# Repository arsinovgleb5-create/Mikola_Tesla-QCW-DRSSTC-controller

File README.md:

# QCW DRSSTC controller v5.9 (ESP32) — firmware, display and control board

**Author: Mikola_Tesla · License: [CC BY 4.0](https://creativecommons.org/licenses/by/4.0/)** — share and adapt freely, just credit the author (see `LICENSE`).

A hand-held controller ("interrupter + ramp generator") for a QCW DRSSTC Tesla coil.
An ESP32 DevKit generates the ramp envelope for the buck modulator and the interrupter
gate signal, reads seven knobs and three buttons, and shows the ramp shape on a small
touch-screen board (ESP32-2432S028R, "Cheap Yellow Display"). Both signals leave the
controller over plastic optical fiber (HFBR transmitters), so the controller has no
galvanic connection to the bridge.

Everything here is hand-made-friendly: a single-sided PCB for toner transfer, through-hole
resistors, DIP drivers, wide tracks and holes.

```
firmware/
  generator/QCW_GENERATOR_ESP32/QCW_GENERATOR_ESP32.ino   ramp generator + interrupter (ESP32 DevKit V1, 30-pin)
  display/cyd_ramp_view/cyd_ramp_view.ino                 ramp viewer for the CYD display (I2C slave)
  display/cyd_ramp_view/User_Setup_CYD.h                  TFT_eSPI configuration for the CYD board
hardware/control_board/
  kicad/                                                  KiCad 10 project (schematic + PCB + own libraries)
  output/schematic.pdf, schematic.png                     schematic, rev. E
  output/bottom_copper_1to1.pdf (+ _mirrored)             copper artwork 1:1 for toner transfer
  output/top_assembly.pdf, bottom_assembly.pdf            part placement, jumper wires (red), labels
  output/top_silkscreen_1to1.pdf, drill_map.pdf           optional silkscreen print, drill map
  output/gerbers.zip                                      Gerber + Excellon in case you order the board
  output/BOM.csv, jumper_wires.json                       parts list, jumper wire list
  output/3d_top.png, 3d_bottom.png, bottom_copper.png     pictures
```

## 1. How the system is put together

```
 knobs (7 pots) ----\
 FIRE / AUTO -------+--> ESP32 DevKit --> TC4420 U2 --> fiber TX "RAMP"  ~~~~> driver board (buck modulator)
 E-STOP (2 groups) -/        |     \---> TC4420 U1 --> fiber TX "INT"   ~~~~> driver board (bridge enable)
                             |  I2C
                             v
                    CYD display (ramp preview, status, supply voltmeter)
```

* **Ramp** — PWM on GPIO19 (MCPWM, 25 kHz carrier by default, `PWM_TOP`). The duty cycle follows the
  envelope: a "wick" step at the start, a rise to the peak, a knee, then a fall. The buck modulator on the
  driver board turns this PWM into the bus voltage envelope.
* **Interrupter** — GPIO4, enables the bridge for the duration of the pulse.
* **One mode**: single QCW ramp pulses, fired by FIRE or repeated by AUTO at the BPS rate (0.5 … 15 pulses/s).
* **E-STOP** — one mushroom switch with two contact groups. Group A (normally open) pulls GPIO23 to ground;
  that pin is also the MCPWM hardware fault input, so the ramp stops in hardware before software reacts.
  Group B (normally closed) is wired in series with the interrupter driver input and cuts the bridge enable
  signal physically.
* **Display link** — I2C, 250 kHz (`LINK_FREQ_HZ`, the same value in both sketches; lower it if your cable is
  long), the generator is the master, the display is a slave at address 0x2A. The link is one-way: the display
  only draws what it receives. Without a STATUS frame for 2 s the display shows OFFLINE / NO LINK.
* **Supply voltmeter** — the display shows the controller 5 V rail (divider on the control board), so a sagging
  battery/buck output is visible before the ESP32 browns out.

## 2. Control board

Single-sided, 85 x 72 mm, all copper on the bottom. Tracks 0.8 mm, clearance 0.6 mm, ground pour on the bottom
with thermal reliefs. Holes: pin headers 1.1 mm, DIP/resistors 1.0 mm, screw terminal 1.6 mm, four M4 mounting
holes (4.3 mm) at (5,6), (80,6), (4.5,67.5), (81,63) mm from the top-left corner.

Parts on top: ESP32 DevKit V1 30-pin in two 1x15 socket headers, two TC4420 DIP-8 drivers, 13 through-hole
resistors 0.25 W (7.62 mm pitch), pin headers, a 2-way screw terminal. Five capacitors (C8…C12) are SMD 1206
and are soldered on the copper (bottom) side — the only SMD parts. See `output/BOM.csv`.

Where tracks cannot cross on one layer, insulated **jumper wires** run on the top side: 30 short pieces
through 29 holes (0.8 mm), the longest one 26 mm. Both ends of one wire carry the same label on the board
(`W1 GND`, `W2 SCL`, …, `W11 ESTOP_B2`); `output/jumper_wires.json` lists every segment with coordinates and
`output/top_assembly.pdf` shows them in red. Holes labelled with the same `Wn` are joined by one wire, chain style.

Making it by toner transfer: print `bottom_copper_1to1.pdf` at 100 % (it is drawn as seen from the top, so
laying the print face-down on the bottom copper mirrors it correctly; use the `_mirrored` file if your
process needs the opposite). Etch, drill, solder the SMD capacitors first, then the jumper wires, then
resistors, sockets, headers and the terminal. Before inserting the ESP32 check that +5V–GND and 3V3–GND are not
shorted.

### Connectors (all 2.54 mm pin headers except J9)

| Conn. | Function | Pins | Location |
|---|---|---|---|
| J1 | knobs (1x9) | 1 = 3V3 rail, 2 = AMPL, 3 = WICK, 4 = FALL, 5 = U, 6 = PW, 7 = BPS, 8 = T, 9 = GND rail | left edge |
| J3 | AUTO button | 1 = signal (GPIO17), 2 = GND | top edge |
| J2 | FIRE button | 1 = signal (GPIO16), 2 = GND | top edge |
| J4 | E-STOP group A (NO) | 1 = GPIO23 (ESTOP_A), 2 = GND | top edge |
| J5 | display (1x5) | 1 = GND, 2 = SCL, 3 = SDA, 4 = VM (voltmeter), 5 = +5V | top edge |
| J8 | E-STOP group B (NC) | 1, 2 = in series with U1 input (no polarity) | bottom edge |
| J7 | fiber TX "INT" (bridge enable) | A = anode, K = cathode | bottom edge |
| J6 | fiber TX "RAMP" (buck modulator) | A = anode, K = cathode | bottom edge |
| J9 | +5 V input, screw terminal | 1 = +5V, 2 = GND | bottom-right corner |

Every pin function is printed on the board next to the pin.

## 3. Wiring guide (what goes where)

**Knobs.** Seven 10 k linear pots, no extra resistors. The 3V3 rail (J1.1) goes to the first pot and is
daisy-chained from pot to pot; the GND rail (J1.9) the same. Each wiper goes with one wire straight to its
J1 pin. Knob → pin → ESP32 GPIO:

| Knob | J1 pin | GPIO | Meaning |
|---|---|---|---|
| AMPL | 2 | 34 | peak power of the ramp |
| WICK | 3 | 35 | starting step ("wick") at the beginning of the ramp |
| FALL | 4 | 32 | fall of the ramp after the peak |
| U | 5 | 33 | knee position on the power axis |
| PW | 6 | 25 | pulse width |
| BPS | 7 | 26 | pulse repetition rate in AUTO |
| T | 8 | 27 | knee position on the time axis |

**Buttons.** FIRE to J2 and AUTO to J3, one contact to the signal pin, the other to GND; pull-ups are inside
the ESP32. E-STOP: contact group A (normally open) to J4, group B (normally closed) to J8, two separate 2-wire
cables.

**Display (CYD).** Five wires from J5:

| J5 | → CYD | Note |
|---|---|---|
| 1 GND | CN1.GND | common ground |
| 2 SCL | CN1.IO22 | 4.7 k pull-ups to 3.3 V are on the control board |
| 3 SDA | CN1.IO27 | |
| 4 VM | P3.IO35 | voltmeter input, divider 10 k / 10 k on the control board |
| 5 +5V | CYD 5 V (USB connector or VIN pad) | |

CN1.3V3 is not used.

**Fiber transmitters (HFBR-1412 / HFBR-1414).** Two wires per transmitter to J6 (RAMP) and J7 (INT):
A = anode = transmitter pins 2, 6 and 7 tied together; K = cathode = transmitter pin 3. Pins 1, 4, 5, 8 are
unused. The transmitter is just an LED: ~60 mA comes from the TC4420 through two 100 ohm resistors in parallel,
no separate supply. Keep these wires short and twisted. On the driver board the HFBR-2412 receivers are powered
from that board (pin 2 = Vcc 5 V, pins 3 and 7 = common, pin 6 = output); light = bridge enabled, a broken
fiber = dark = inhibit.

**Power.** Any clean 5 V source feeds the screw terminal J9 (1 = +5V, 2 = GND); the author uses a buck
 converter from a 12 V battery. On the board
5 V goes to the ESP32 VIN, to both TC4420 and to the display (J5.5). 3.3 V for the knobs and the I2C pull-ups
comes from the ESP32 module regulator.

**Grounds.** All grounds meet on the board's ground pour: buck minus (J9.2), display (J5.1 only), knobs
(J1.9 rail), buttons, transmitter cathodes. Do not run extra ground wires between external parts. The
controller must never share ground with the bridge or the buck modulator — that is what the fiber is for. If
the enclosure is metal, connect it to J9.2 with a single wire.

## 4. Building and flashing the firmware

Both sketches are for the **Arduino IDE / arduino-cli with the ESP32 Arduino core 3.x** (the author builds with
3.3.x; a few comments in the code describe behaviour observed with that version).

### Generator (`QCW_GENERATOR_ESP32.ino`)

* Board: "ESP32 Dev Module". CPU frequency 240 MHz, partition scheme "Huge APP", flash frequency 80 MHz.
  The firmware checks the CPU frequency at start and refuses to run at the wrong one.
* No external libraries; the MCPWM driver and FreeRTOS come with the core.
* Pin map is in the `PIN DEFINITIONS` section of the sketch. Where to change things: carrier frequency —
  `PWM_TOP` (16 MHz / PWM_TOP, 640 = 25 kHz). A higher carrier makes the ramp smoother (less choke ripple,
  finer envelope steps in time) but loads the gate driver, the gate DC-DC and the IGBT brick harder — switching
  losses grow linearly with frequency. The frequency table in the sketch was computed for the author's buck
  (FF200R12KE4 brick, Rg 15 ohm, 650 V, 800 uH choke, 2 W gate DC-DC) — recompute it for your parts; pulse-rate limits — `BPS_MIN_X10` / `BPS_MAX_X10`; bus
  voltage and wick in volts — `BUS_VOLTAGE`, `WICK_VOLTAGE` (the wick duty is computed from them). These two,
  the alpha (bus sag) compensation and the pot end-stop constants are build-specific: set them for your coil.
* The serial monitor (115200) prints the computed configuration at start and every state change
  (ARMED, AUTO, ESTOP, faults).

### Display (`cyd_ramp_view.ino`)

* Board: "ESP32 Dev Module", upload speed **230400**. On the author's CYD the CH340 USB-serial chip fails at
  460800 and above; other batches may accept more, but 230400 always works.
* Library: TFT_eSPI 2.5.x. Copy `User_Setup_CYD.h` over `Arduino/libraries/TFT_eSPI/User_Setup.h` (rename it
  to `User_Setup.h`), the sketch cannot configure the library by itself. The file has `TFT_INVERSION_ON`
  because this panel variant is inverted (white background otherwise); comment it out if your panel shows
  inverted colours.
* The display draws: mode (IDLE / ARMED / AUTO / E-STOP / OFFLINE), LINK OK / NO LINK with the shot and CRC
  error counters, the ramp curve on a fixed 0…25 ms time axis, and under it peak and wick in volts, fall, BPS,
  pulse width, PWM steps. The supply voltage is shown in small font in the top-left block.

### Link protocol (for anyone who wants another display)

Frame: `[type][len][payload…][crc8]`, CRC-8 over type+len+payload, polynomial 0x07, init 0x00, MSB first.

* `0x00 STATUS` (6 bytes): fw_major, fw_minor, flags (0x01 ARMED, 0x02 AUTO, 0x04 ESTOP, 0x08 PREVIEW_READY),
  pulses_lo, pulses_hi, 0. Sent every 100 ms — this is the heartbeat; without it the display shows NO LINK.
* `0x10|gen META` (22 bytes, uint16 little-endian): pulse_width_ms, bps_x10, peak_duty, wick_offset, fall_x100,
  tscale_x100, uscale_x100, pwm_top, bus_voltage, rise_end_x10000, then two bytes: points (80), rise_points (64).
  `gen` is a 3-bit generation counter of the preview.
* `0x40|gen<<3|n CHUNK`: curve points in three chunks of 30, 30 and 20 (n = 0, 1, 2 → points 0–29, 30–59, 60–79),
  each point is the duty 0…255 relative to pwm_top. The time grid is not uniform: the first rise_points (64) points
  cover the rise, the remaining 16 cover the fall.

## 5. Supply voltmeter

R18 (10 k) from +5 V to the VM node and R19 (10 k) from VM to GND on the control board; VM goes through J5.4
to the CYD input IO35 (ADC1, 11 dB attenuation, input only). In `cyd_ramp_view.ino`: `VMETER_DIV = 2.0`
(= (R_top + R_bottom) / R_bottom), green above `VMETER_OK_V` (4.8 V), yellow between, red below
`VMETER_LOW_V` (4.5 V). If the input is below 1 V (no divider connected) nothing is shown. To watch a 12 V
battery instead, use 100 k / 22 k and set `VMETER_DIV` to 5.55.

## 6. Safety

A Tesla coil is lethal. Do not run this without understanding the schematic and the driver-side protections.
The firmware has a task watchdog, forces all outputs low at start-up, checks the hardware fault path of the
MCPWM at boot and refuses to arm if anything is inconsistent — but none of that replaces a proper E-STOP in
the mains path and an isolated, fiber-coupled driver.

## 7. Build configuration

All numbers that depend on your coil are collected in one `BUILD CONFIGURATION` block at the top of
`QCW_GENERATOR_ESP32.ino`: bus voltage, carrier frequency (`PWM_TOP`), ramp ceiling, alpha compensation, wick
voltage and margins, pulse-width and BPS ranges, buck stage timings, knob end stops and the link speed.
Everything else is derived from them by the preprocessor and checked by `static_assert`s — change a value,
rebuild, and the whole firmware follows. The display sketch has the same kind of block for the voltmeter
divider, thresholds, auto refresh and link speed/timeout.

## 8. License

Copyright (c) 2026 Mikola_Tesla. Released under CC BY 4.0: you may share and modify everything here, including
commercially, as long as you credit the author and state your changes. No warranty.

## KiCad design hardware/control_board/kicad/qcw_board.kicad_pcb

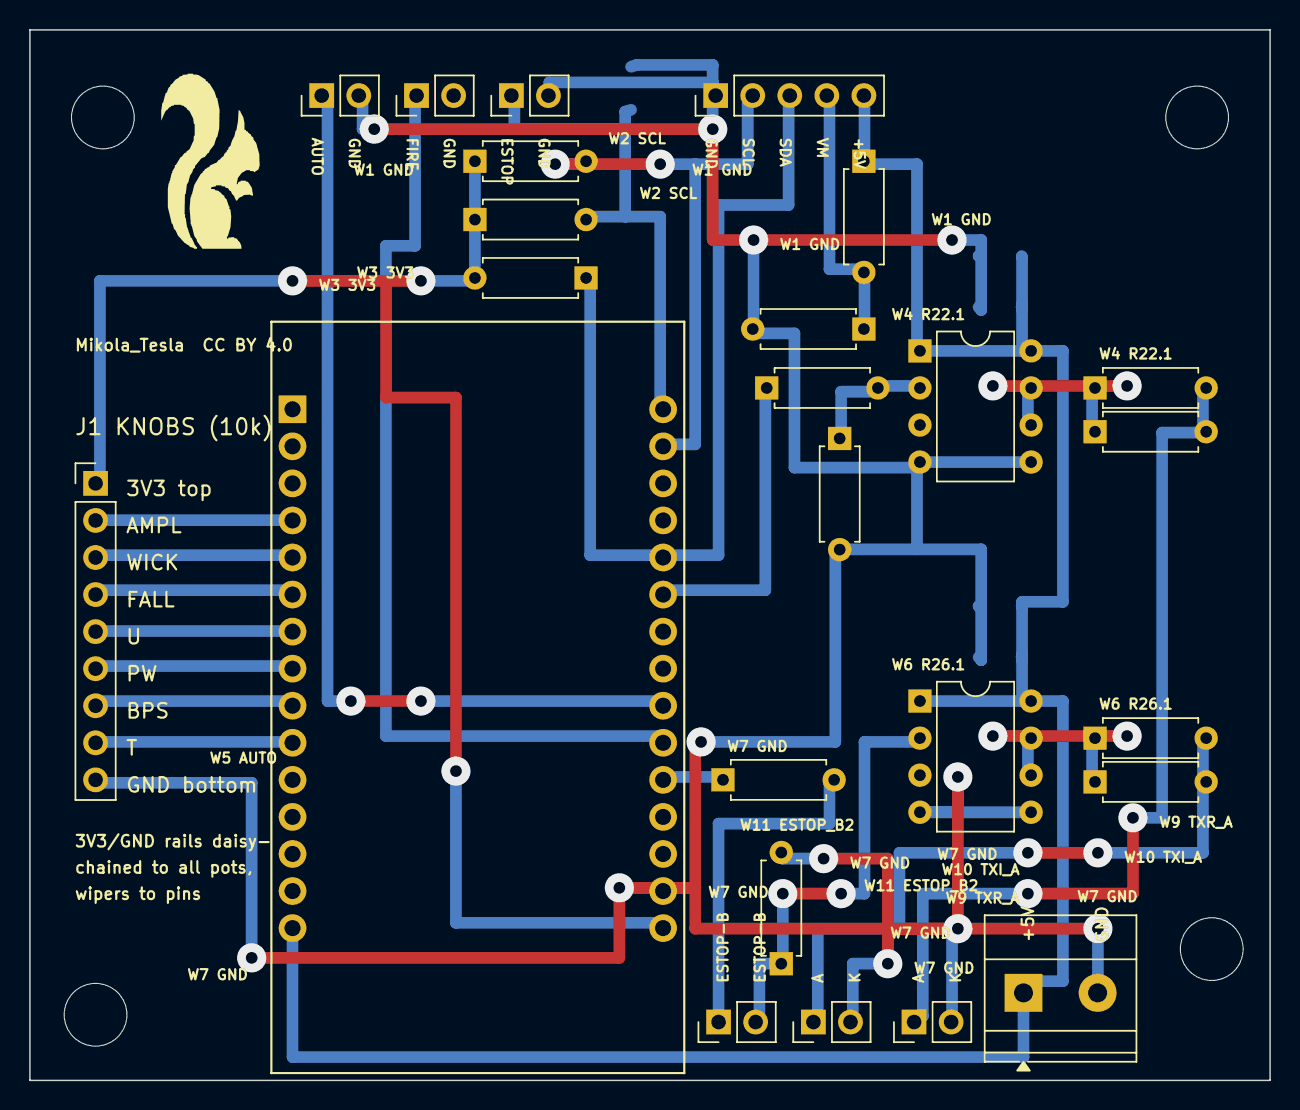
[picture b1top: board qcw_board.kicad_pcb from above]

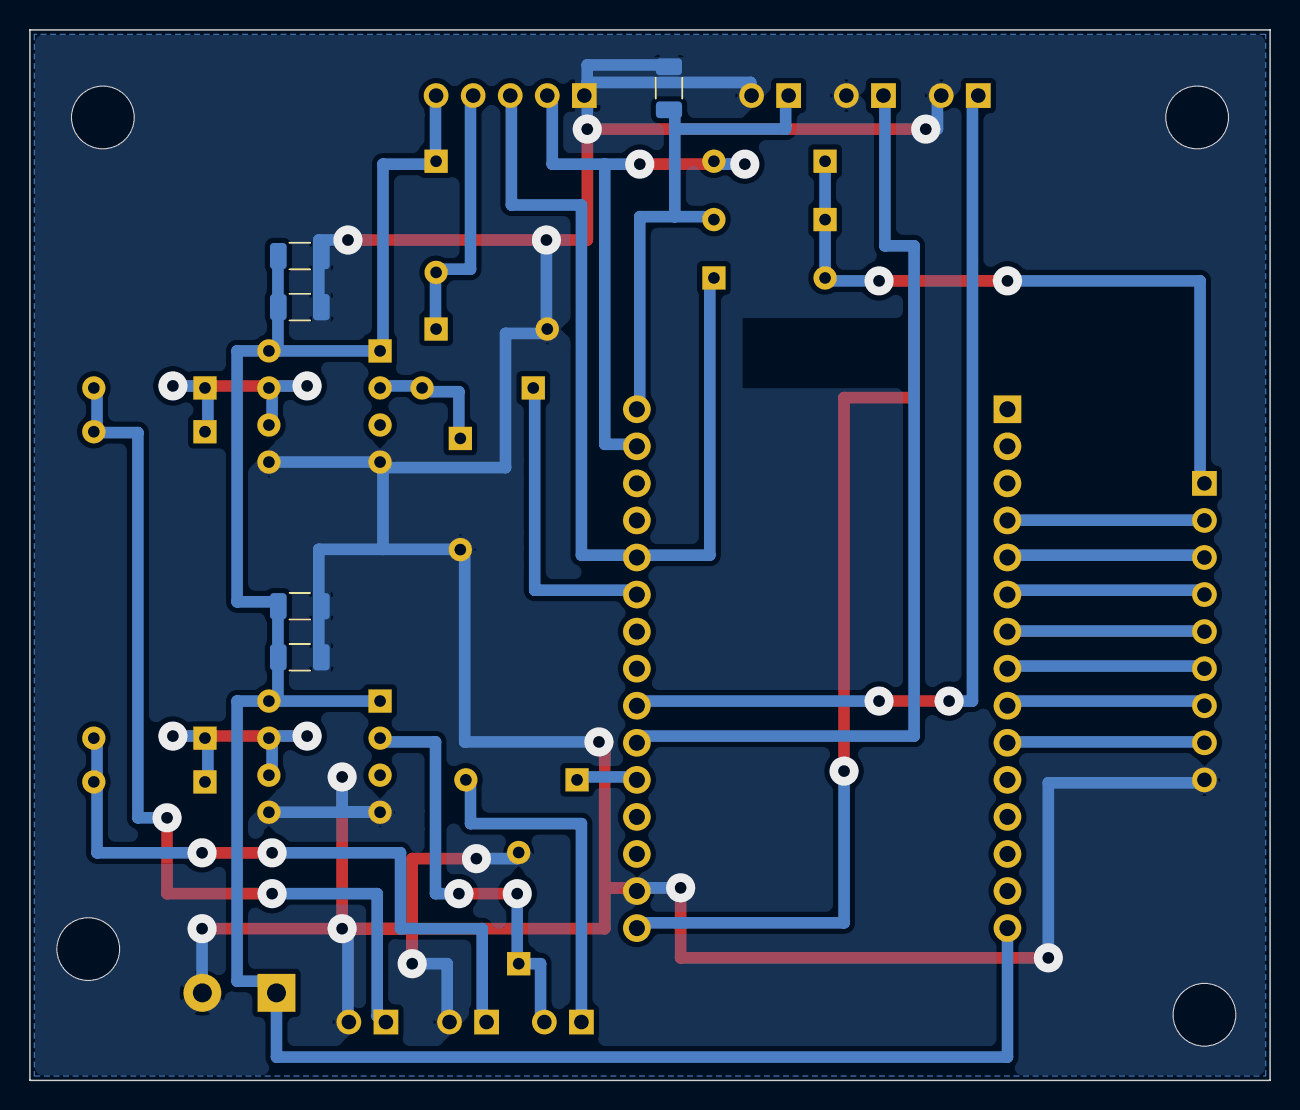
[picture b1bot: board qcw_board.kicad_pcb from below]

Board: 2 copper layers, 85.0 x 72.0 mm, 34 parts (5 on the bottom side), 25 nets.

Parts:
A1: ESP32 DevKit 30 pin; ESP32_DevKit_30
C8, C10, C12: 100n; C_1206_3216Metric
C9, C11: 1u; C_1206_3216Metric
H1, H2, H3, H4: MountingHole_4.3mm_M4
J1: KNOBS (potentiometers); PinHeader_1x09_wide
J2: FIRE; PinHeader_1x02_wide
J3: AUTO; PinHeader_1x02_wide
J4: E-STOP A; PinHeader_1x02_wide
J5: SCREEN; PinHeader_1x05_wide
J6, J7: TX; PinHeader_1x02_wide
J8: E-STOP B; PinHeader_1x02_wide
J9: +5V / GND; TerminalBlock_2_wide
R15, R16, R17: 4.7k; R_Axial_P7.62_wide
R18, R19, R21, R25: 10k; R_Axial_P7.62_wide
R20, R24: 150; R_Axial_P7.62_wide
R22, R23, R26, R27: 100; R_Axial_P7.62_wide
U1, U2: TC4420; DIP-8_W7.62mm_wide

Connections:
3V3: A1.30, J1.1, R15.1, R16.1, R17.2
+5V: A1.15, C9.2, C10.2, C11.2, C12.2, J5.5, J9.1, R18.1, U1.1, U1.8, U2.1, U2.8
/AMPL_W: A1.4, J1.2
/AUTO: A1.24, J3.1
/BPS_W: A1.9, J1.7
/ESTOP_A: A1.16, C8.1, J4.1, R15.2
/ESTOP_B1: J8.1, R24.2
/ESTOP_B2: J8.2, R25.1, U1.2
/FALL_W: A1.6, J1.4
/FIRE: A1.25, J2.1
/PW_W: A1.8, J1.6
/SCL: A1.17, J5.2, R16.2
/SDA: A1.20, J5.3, R17.1
/TXI_A: J7.1, R26.2, R27.2
/TXR_A: J6.1, R22.2, R23.2
/T_W: A1.10, J1.8
/U_W: A1.7, J1.5
/VMETER: J5.4, R18.2, R19.1
/WICK_W: A1.5, J1.3
GND: A1.29, C8.2, C9.1, C10.1, C11.1, C12.1, J1.9, J2.2, J3.2, J4.2, J5.1, J6.2, J7.2, J9.2, R19.2, R21.2, R25.2, U1.4, U1.5, U2.4, U2.5
unnamed: A1.26, R24.1
unnamed: A1.21, R20.1
unnamed: R22.1, R23.1, U2.6, U2.7
unnamed: R26.1, R27.1, U1.6, U1.7
unnamed: R20.2, R21.1, U2.2

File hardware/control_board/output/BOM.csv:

Qty,References,Value,Footprint,Note
3,C8 C10 C12,100n,Capacitor_SMD:C_1206_3216Metric,"SMD 1206 X7R capacitor (100n: 50 V; 1u: 16 V or more), soldered on the copper (bottom) side"
2,C9 C11,1u,Capacitor_SMD:C_1206_3216Metric,"SMD 1206 X7R capacitor (100n: 50 V; 1u: 16 V or more), soldered on the copper (bottom) side"
2,U1 U2,TC4420,QCW:DIP-8_W7.62mm_wide,TC4420CPA DIP-8 (DIP-8 socket optional); 1.0 mm holes
1,A1,ESP32 DevKit 30 pin,QCW:ESP32_DevKit_30,two 1x15 female headers 2.54 mm; DOIT ESP32 DevKit V1 30-pin module (rows 25.4 mm apart); 1.2 mm holes
1,J3,AUTO,QCW:PinHeader_1x02_wide,2.54 mm male pin header; 1.1 mm holes
1,J4,E-STOP A,QCW:PinHeader_1x02_wide,2.54 mm male pin header; 1.1 mm holes
1,J8,E-STOP B,QCW:PinHeader_1x02_wide,2.54 mm male pin header; 1.1 mm holes
1,J2,FIRE,QCW:PinHeader_1x02_wide,2.54 mm male pin header; 1.1 mm holes
2,J6 J7,TX,QCW:PinHeader_1x02_wide,2.54 mm male pin header; 1.1 mm holes
1,J5,SCREEN,QCW:PinHeader_1x05_wide,2.54 mm male pin header; 1.1 mm holes
1,J1,KNOBS (potentiometers),QCW:PinHeader_1x09_wide,2.54 mm male pin header; 1.1 mm holes
4,R22 R23 R26 R27,100,QCW:R_Axial_P7.62_wide,"through-hole resistor 0.25 W, 7.62 mm pitch; 1.0 mm holes"
4,R18 R19 R21 R25,10k,QCW:R_Axial_P7.62_wide,"through-hole resistor 0.25 W, 7.62 mm pitch; 1.0 mm holes"
2,R20 R24,150,QCW:R_Axial_P7.62_wide,"through-hole resistor 0.25 W, 7.62 mm pitch; 1.0 mm holes"
3,R15 R16 R17,4.7k,QCW:R_Axial_P7.62_wide,"through-hole resistor 0.25 W, 7.62 mm pitch; 1.0 mm holes"
1,J9,+5V / GND,QCW:TerminalBlock_2_wide,"2-way screw terminal, 5.08 mm pitch; 1.6 mm holes"

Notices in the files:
hardware/control_board/kicad/qcw_board.kicad_pcb:
Mikola_Tesla  CC BY 4.0
